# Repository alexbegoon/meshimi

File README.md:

<div align="center" markdown="1">

<h1>Meshimi</h1>

<b>Open Hardware & Open Source Multi-Protocol Wireless Module</b>

</div>

Meshimi empowers your Flipper Zero with advanced mesh networking capabilities, utilizing Meshtastic, LoRaWAN, WiFi6 and Bluetooth protocols.

## 📁 Repository Structure
- [`hardware/`](hardware) - PCB schematics, layouts, and production files
- [`mechanical/`](mechanical) - 3D models, enclosures, and assembly guides
- [`firmware/`](firmware) - Core firmware and code examples
- [`software/`](software) - Flipper Zero app and configuration tools
- [`documentation/`](documentation) - Documentation, guides, and certifications
- [`assets/`](assets) - Logos, photos, and marketing materials

## 📖 Documentation

### 🛡️ Certifications
Meshimi project utilizes pre-certified RF modules to ensure regulatory compliance. 
The corresponding CE, FCC, and other certification documentation for these modules are available 
in the [certifications](documentation/certifications) directory. 

We are committed to maintaining full regulatory compliance.

_Seeed XIAO ESP32-C6 module_ is used in Meshimi, which has the following certifications:

1. [Seeed-XIAO-ESP32C6-CE-Verification.pdf](documentation/certifications/Seeed-XIAO-ESP32C6-CE-Verification.pdf)

2. [Seeed-XIAO-ESP32C6-EU-Declaration.pdf](documentation/certifications/Seeed-XIAO-ESP32C6-EU-Declaration.pdf)

3. [Seeed-XIAO-ESP32C6-FCC-Declaration.pdf](documentation/certifications/Seeed-XIAO-ESP32C6-FCC-Declaration.pdf)

4. [Seeed-XIAO-ESP32C6-TELEC-Certificate.pdf](documentation/certifications/Seeed-XIAO-ESP32C6-TELEC-Certificate.pdf)

5. [Seeed-XIAO-ESP32C6-UK-Declaration.pdf](documentation/certifications/Seeed-XIAO-ESP32C6-UK-Declaration.pdf)

6. [Seeed-XIAO-Series-RoHS-Certificate.pdf](documentation/certifications/Seeed-XIAO-Series-RoHS-Certificate.pdf)

_Seeed Wio SX-1262 module_ is used in Meshimi, which has the following certifications:

1. [Seeed-Wio-SX1262-CE-Verification.pdf](documentation/certifications/Seeed-Wio-SX1262-CE-Verification.pdf)

2. [Seeed-Wio-SX1262-EU-Declaration.pdf](documentation/certifications/Seeed-Wio-SX1262-EU-Declaration.pdf)

3. [Seeed-Wio-SX1262-FCC-Authorization.pdf](documentation/certifications/Seeed-Wio-SX1262-FCC-Authorization.pdf)

4. [Seeed-Wio-SX1262-TELEC-Certificate.pdf](documentation/certifications/Seeed-Wio-SX1262-TELEC-Certificate.pdf)

5. [Seeed-Wio-SX1262-UK-Declaration.pdf](documentation/certifications/Seeed-Wio-SX1262-UK-Declaration.pdf)

6. [Seeed-Wio-SX1262-RoHS-Certificate.pdf](documentation/certifications/Seeed-Wio-SX1262-RoHS-Certificate.pdf)

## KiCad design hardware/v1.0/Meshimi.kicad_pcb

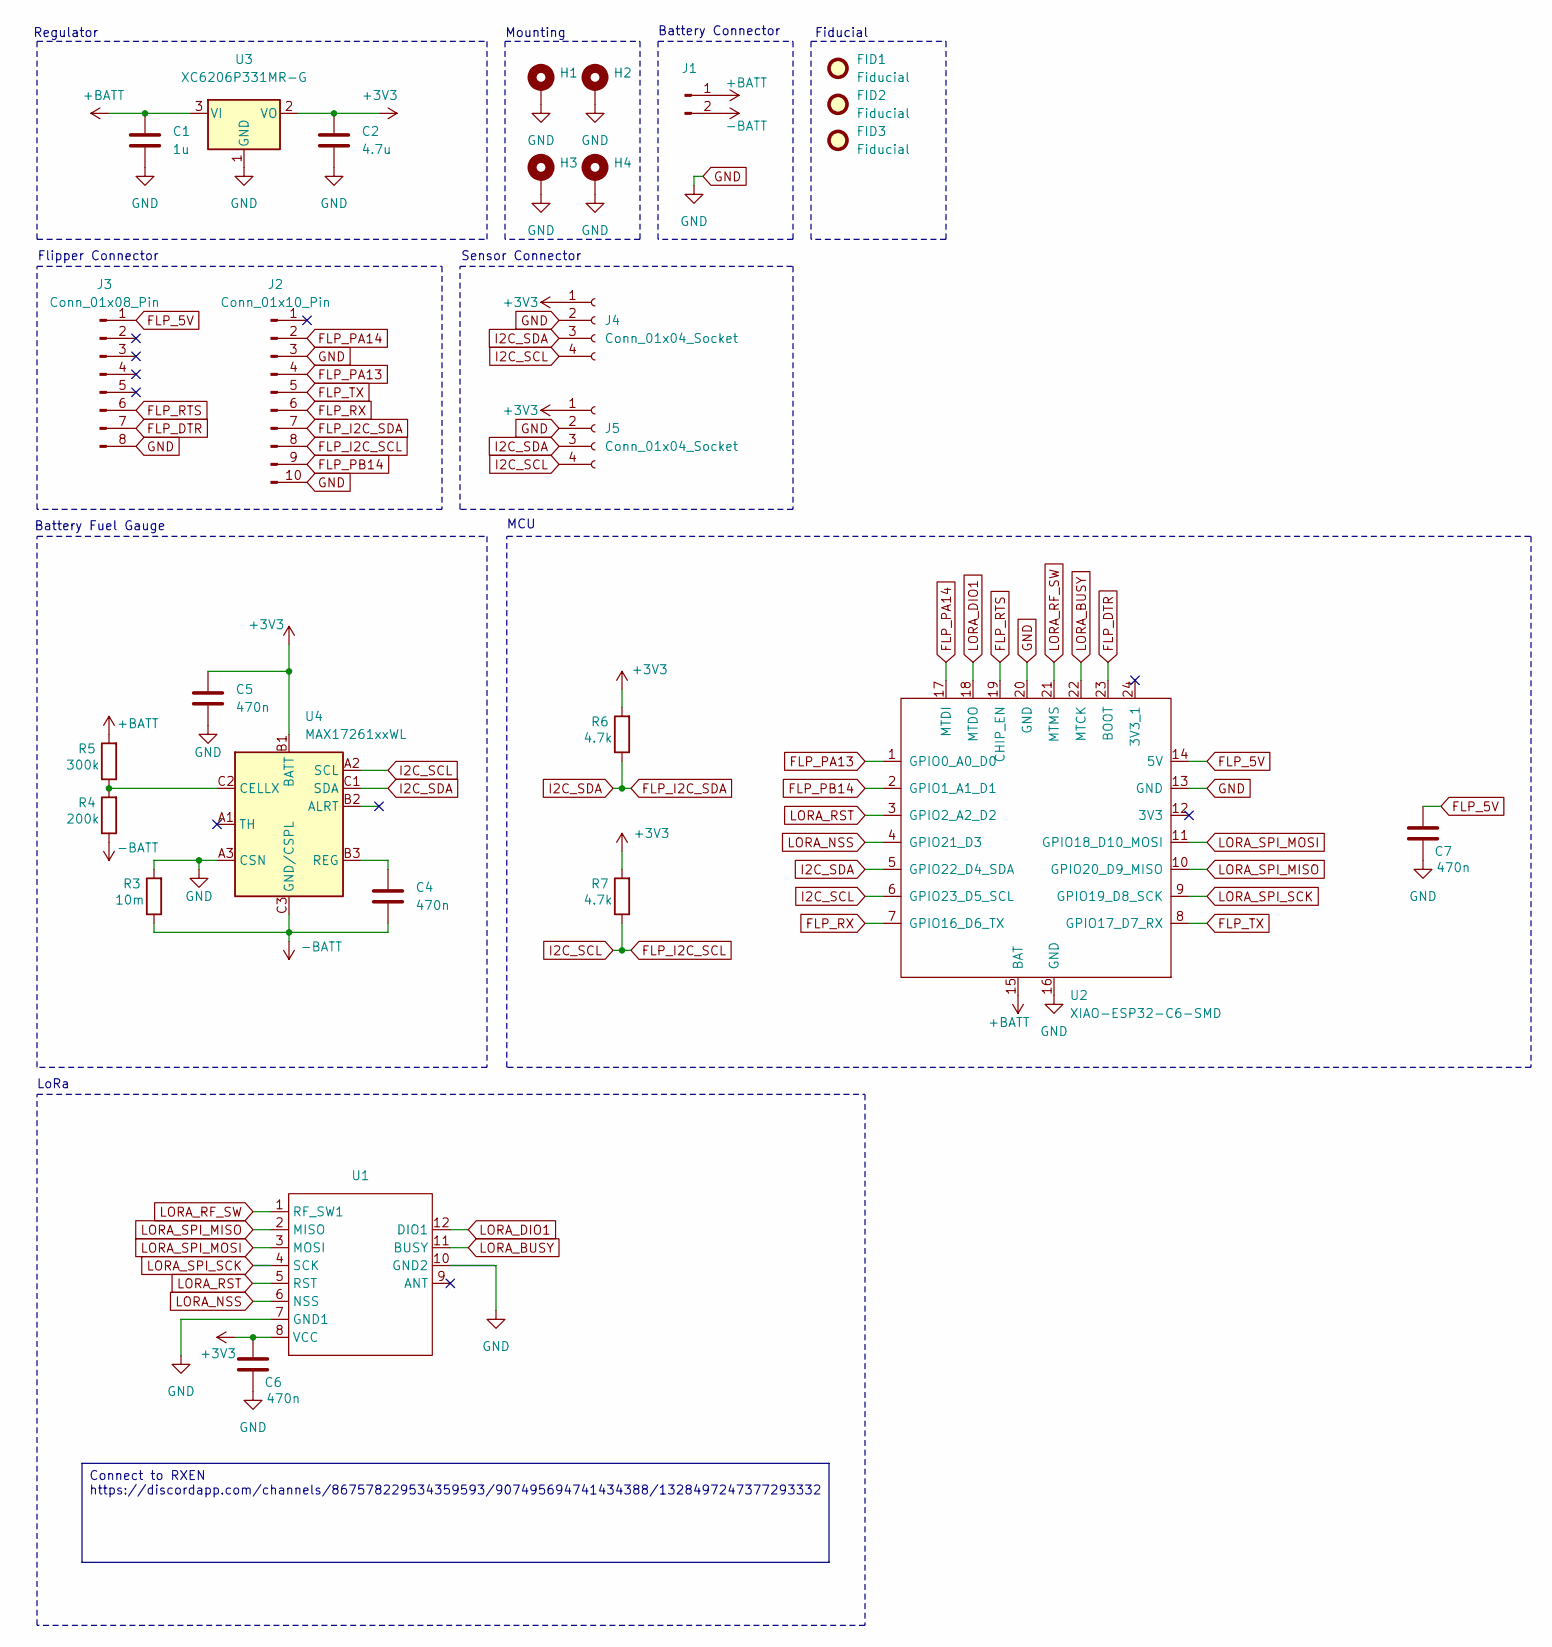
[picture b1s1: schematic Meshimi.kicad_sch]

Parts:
C1: 1u; C_0805_2012Metric
C2: 4.7u; C_0805_2012Metric
C4, C5, C6, C7: 470n; C_0805_2012Metric
FID1, FID2, FID3: Fiducial; Fiducial_1mm_Mask2mm
H1, H2, H3, H4: MountingHole_3mm_Pad_Via
J1: JST_EH_B2B-EH-A_1x02_P2.50mm_Vertical
J2: Conn_01x10_Pin; PinHeader_1x10_P2.54mm_Horizontal
J3: Conn_01x08_Pin; PinHeader_1x08_P2.54mm_Horizontal
J4, J5: Conn_01x04_Socket; PinHeader_1x04_P2.00mm_Vertical
R3: 10m; R_0402_1005Metric
R4: 200k; R_0402_1005Metric
R5: 300k; R_0402_1005Metric
R6, R7: 4.7k; R_0402_1005Metric
U1: Wio-SX1262
U2: XIAO-ESP32-C6-SMD; XIAO-ESP32C6-SMD
U3: XC6206P331MR-G; SOT-23
U4: MAX17261xxWL; Maxim_WLP-9_1.595x1.415_Layout3x3_P0.4mm_Ball0.27mm_Pad0.25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

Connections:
+3V3: C2.1, C5.1, C6.1, J4.1, J5.1, R6.2, R7.2, U1.8 (VCC), U3.2 (VO), U4.B1 (BATT)
+BATT: C1.1, J1.1, R5.2, U2.15 (BAT), U3.3 (VI)
-BATT: C4.2, J1.2, R3.1, R4.1, U4.C3 (GND/CSPL)
FLP_5V: C7.1, J3.1, U2.14 (5V)
FLP_DTR: J3.7, U2.23 (BOOT)
FLP_I2C_SCL: J2.8, J4.4, J5.4, R7.1, U2.6 (GPIO23_D5_SCL), U4.A2 (SCL)
FLP_I2C_SDA: J2.7, J4.3, J5.3, R6.1, U2.5 (GPIO22_D4_SDA), U4.C1 (SDA)
FLP_PA13: J2.4, U2.1 (GPIO0_A0_D0)
FLP_PA14: J2.2, U2.17 (MTDI)
FLP_PB14: J2.9, U2.2 (GPIO1_A1_D1)
FLP_RTS: J3.6, U2.19 (CHIP_EN)
FLP_RX: J2.6, U2.7 (GPIO16_D6_TX)
FLP_TX: J2.5, U2.8 (GPIO17_D7_RX)
GND: C1.2, C2.2, C5.2, C6.2, C7.2, H1.1, H2.1, H3.1, H4.1, J2.3, J2.10, J3.8, J4.2, J5.2, R3.2, U1.7 (GND1), U1.10 (GND2), U2.13 (GND), U2.16 (GND), U2.20 (GND), U3.1 (GND), U4.A3 (CSN)
LORA_BUSY: U1.11 (BUSY), U2.22 (MTCK)
LORA_DIO1: U1.12 (DIO1), U2.18 (MTDO)
LORA_NSS: U1.6 (NSS), U2.4 (GPIO21_D3)
LORA_RF_SW: U1.1 (RF_SW1), U2.21 (MTMS)
LORA_RST: U1.5 (RST), U2.3 (GPIO2_A2_D2)
LORA_SPI_MISO: U1.2 (MISO), U2.10 (GPIO20_D9_MISO)
LORA_SPI_MOSI: U1.3 (MOSI), U2.11 (GPIO18_D10_MOSI)
LORA_SPI_SCK: U1.4 (SCK), U2.9 (GPIO19_D8_SCK)
unnamed: R4.2, R5.1, U4.C2 (CELLX)
unnamed: C4.1, U4.B3 (REG)

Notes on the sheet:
MCU
Flipper Connector
Mounting
Battery Fuel Gauge
Sensor Connector
LoRa
Regulator
Battery Connector
Fiducial
Connect to RXEN https://discordapp.com/channels/867578229534359593/907495694741434388/1328497247377293332

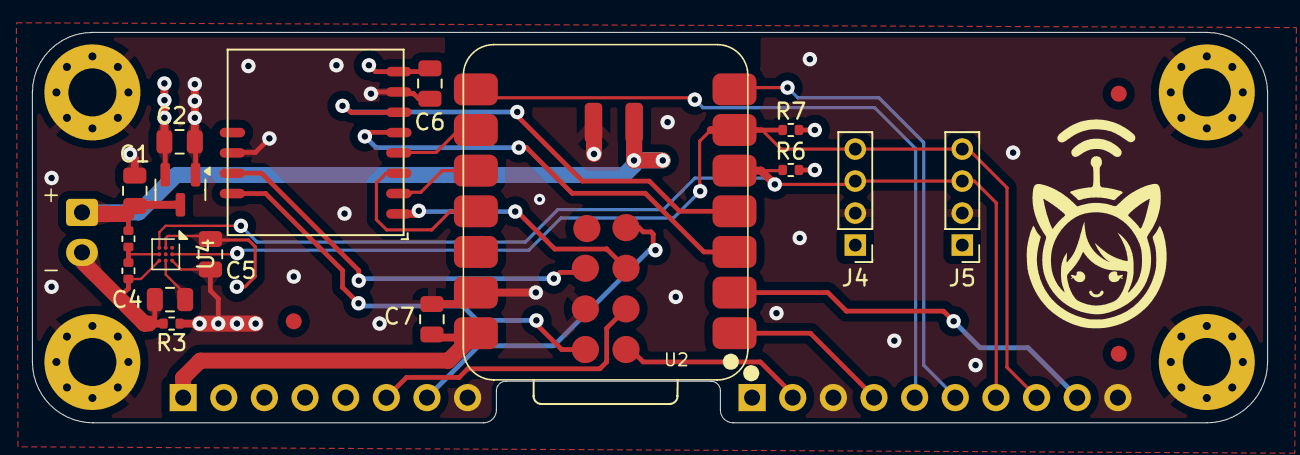
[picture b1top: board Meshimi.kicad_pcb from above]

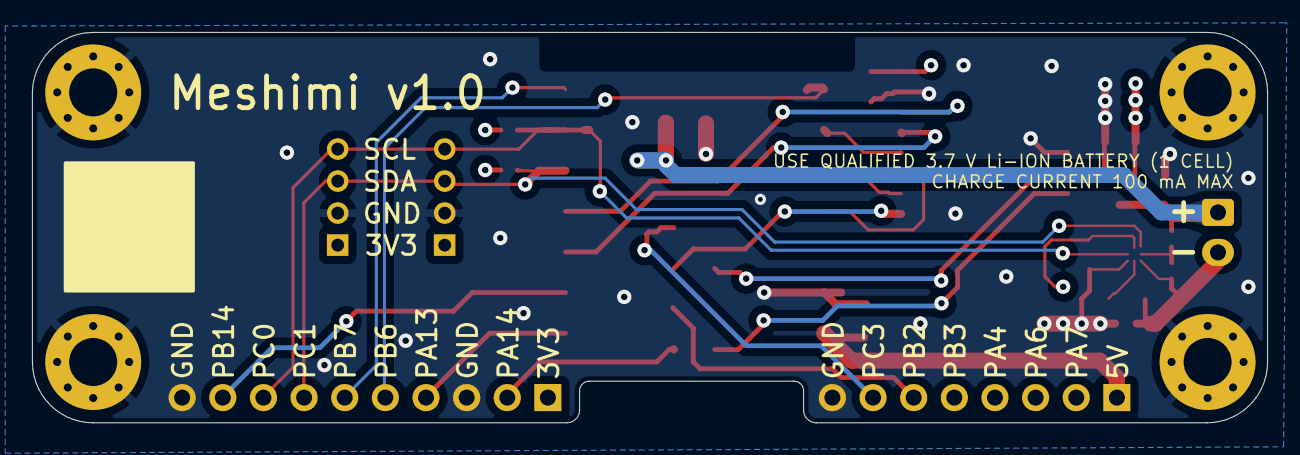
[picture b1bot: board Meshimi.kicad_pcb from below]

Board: 4 copper layers, 77.2 x 24.4 mm, 27 parts (2 on the bottom side), 24 nets.

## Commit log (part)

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2025-07-06 Add initial KiCad project files and configuration
2025-07-20 Update .gitignore and add description link in Meshimi schematic
2025-07-20 Update README.md to include documentation section and certification details
2025-07-20 Add CAD models: enclosure housing/cover and PCB design
2025-07-20 Add documentation for Meshimi module enclosures and Flipper Zero integration
2025-07-21 Rename index.md to README.md and update documentation links
2025-07-21 Update README.md to add additional certification documents
2025-07-21 Update README.md to enhance certification information and regulatory compliance details
2025-07-21 Update docs
2025-07-21 Update README.md to correct Wio certification documents
2025-07-22 Add initial implementation of Meshimi application with configuration and scene management
2025-07-22 Update docker-compose.yaml to use environment variable for firmware path
2025-07-23 Add FUNDING.yml to specify GitHub funding information
2025-07-23 Enhance README.md with improved title formatting and Kickstarter badge
